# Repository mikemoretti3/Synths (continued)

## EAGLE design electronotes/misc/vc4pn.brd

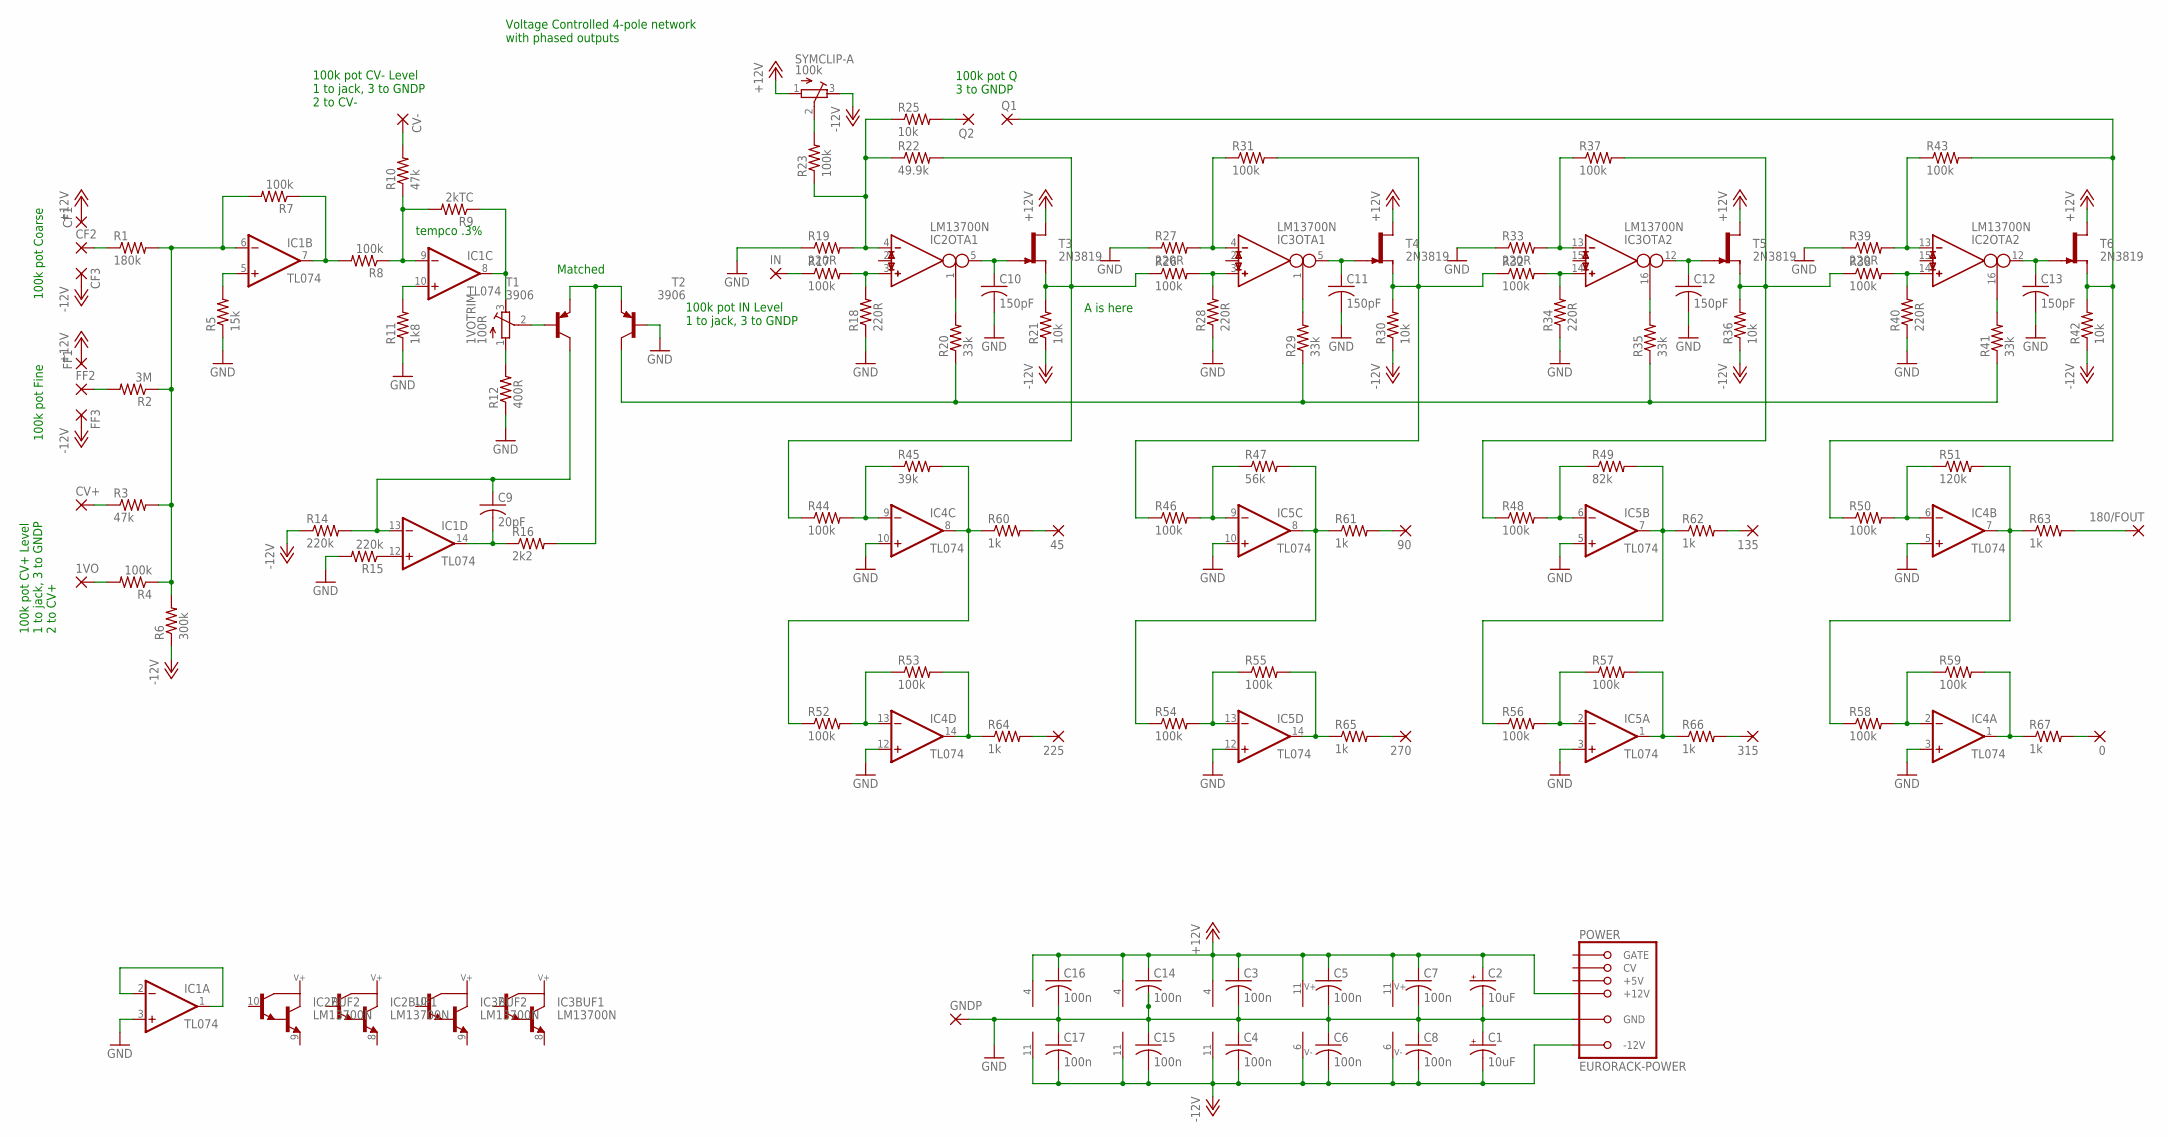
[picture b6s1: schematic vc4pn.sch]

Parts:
0, 1VO, 45, 90, 135, 180/FOUT, 225, 270, 315: 2,54/1,0
1VOTRIM: 100R; RTRIM64W
C1, C2: 10uF; E2,5-5
C3, C4, C5, C6, C7, C8, C14, C15, C16, C17: 100n; C050-025X075
C9: 20pF; C050-025X075
C10, C11, C12, C13: 150pF; C050-025X075
CF1, CF2, CF3: 2,54/1,0
CV+: 2,54/1,0
CV-: 2,54/1,0
FF1, FF2, FF3: 2,54/1,0
GNDP: 2,54/1,0
IC1, IC4, IC5: TL074; DIL14
IC2, IC3: LM13700N; DIL16
IN: 2,54/1,0
POWER: EURORACK-POWER; PINSHRD_PTH_2X8
Q1, Q2: 2,54/1,0
R1: 180k; 0207/2V
R2: 3M; 0207/2V
R3, R10: 47k; 0207/2V
R4, R7, R8, R17, R23, R26, R31, R32, R37, R38, R43, R44, R46, R48, R50, R52, R53, R54, R55, R56, R57, R58, R59: 100k; 0207/2V
R5: 15k; 0207/2V
R6: 300k; 0207/2V
R9: 2kTC; 0207/10
R11: 1k8; 0207/2V
R12: 400R; 0207/2V
R14, R15: 220k; 0207/2V
R16: 2k2; 0207/2V
R18, R19, R27, R28, R33, R34, R39, R40: 220R; 0207/2V
R20, R29, R35, R41: 33k; 0207/2V
R21, R25, R30, R36, R42: 10k; 0207/2V
R22: 49.9k; 0207/2V
R45: 39k; 0207/2V
R47: 56k; 0207/2V
R49: 82k; 0207/2V
R51: 120k; 0207/2V
R60, R61, R62, R63, R64, R65, R66, R67: 1k; 0207/2V
SYMCLIP-A: 100k; RTRIM64W
T1, T2: 3906; TO92-EBC
T3, T4, T5, T6: 2N3819; TO92-

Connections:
+12V: C2.+, C3.1, C5.1, C7.1, C14.1, C16.1, CF1.1, FF1.1, IC1.4 (V+), IC2.11 (7), IC3.11 (7), IC4.4 (V+), IC5.4 (V+), POWER.+12V@1 (+12V), POWER.+12V@2 (+12V), SYMCLIP-A.1 (A), T3.3 (D), T4.3 (D), T5.3 (D), T6.3 (D)
-12V: C1.-, C4.2, C6.2, C8.2, C15.2, C17.2, CF3.1, FF3.1, IC1.11 (V-), IC2.6 (4), IC3.6 (4), IC4.11 (V-), IC5.11 (V-), POWER.-12V@1 (-12V), POWER.-12V@2 (-12V), R6.1, R14.1, R21.1, R30.1, R36.1, R42.1, SYMCLIP-A.3 (E)
GND: C1.+, C2.-, C3.2, C4.1, C5.2, C6.1, C7.2, C8.1, C10.2, C11.2, C12.2, C13.2, C14.2, C15.1, C16.2, C17.1, GNDP.1, IC1.3 (+IN), IC4.3 (+IN), IC4.5 (+IN), IC4.10 (+IN), IC4.12 (+IN), IC5.3 (+IN), IC5.5 (+IN), IC5.10 (+IN), IC5.12 (+IN), POWER.GND@1 (GND), POWER.GND@2 (GND), POWER.GND@3 (GND), POWER.GND@4 (GND), POWER.GND@5 (GND), POWER.GND@6 (GND), R5.1, R11.1, R12.1, R15.2, R18.1, R19.1, R27.1, R28.1, R33.1, R34.1, R39.1, R40.1, T2.B
unnamed: CF2.1, R1.1
unnamed: FF2.1, R2.2
unnamed: CV+.1, R3.1
unnamed: IC1.1 (OUT), IC1.2 (-IN)
unnamed: 1VO.1, R4.2
unnamed: IC1.5 (+IN), R5.2
unnamed: CV-.1, R10.2
unnamed: IC1.6 (-IN), R1.2, R2.1, R3.2, R4.1, R6.2, R7.2
unnamed: IC1.7 (OUT), R7.1, R8.2
unnamed: IC1.9 (-IN), R8.1, R9.2, R10.1
unnamed: 1VOTRIM.3 (E), IC1.8 (OUT), R9.1
unnamed: 1VOTRIM.1 (A), R12.2
unnamed: IC1.10 (+IN), R11.2
unnamed: R16.2, T1.E, T2.E
unnamed: 1VOTRIM.2 (S), T1.B
unnamed: C9.1, IC1.13 (-IN), R14.2, T1.C
unnamed: IC1.12 (+IN), R15.1
unnamed: C9.2, IC1.14 (OUT), R16.1
unnamed: IN.1, R17.1
unnamed: IC2.3 (IN_P), R17.2, R18.2
unnamed: IC2.4 (IN_N), R19.2, R22.1, R23.1, R25.1
unnamed: IC2.1 (I_BIAS), R20.2
unnamed: R20.1, R29.1, R35.1, R41.1, T2.C
unnamed: C10.1, IC2.5 (OUT), T3.2 (G)
unnamed: R21.2, R22.2, R26.1, R44.1, T3.1 (S)
unnamed: IC3.3 (IN_P), R26.2, R28.2
unnamed: R23.2, SYMCLIP-A.2 (S)
unnamed: IC3.4 (IN_N), R27.2, R31.1
unnamed: IC3.1 (I_BIAS), R29.2
unnamed: Q2.1, R25.2
unnamed: C11.1, IC3.5 (OUT), T4.2 (G)
unnamed: R30.2, R31.2, R32.1, R46.1, T4.1 (S)
unnamed: IC4.9 (-IN), R44.2, R45.1
unnamed: IC5.9 (-IN), R46.2, R47.1
unnamed: IC3.14 (IN_P), R32.2, R34.2
unnamed: IC3.13 (IN_N), R33.2, R37.1
unnamed: IC3.16 (I_BIAS), R35.2
unnamed: C12.1, IC3.12 (OUT), T5.2 (G)
unnamed: R36.2, R37.2, R38.1, R48.1, T5.1 (S)
unnamed: IC5.6 (-IN), R48.2, R49.1
unnamed: IC4.6 (-IN), R50.2, R51.1
unnamed: IC2.14 (IN_P), R38.2, R40.2
unnamed: IC2.13 (IN_N), R39.2, R43.1
unnamed: IC2.16 (I_BIAS), R41.2
unnamed: C13.1, IC2.12 (OUT), T6.2 (G)
unnamed: Q1.1, R42.2, R43.2, R50.1, T6.1 (S)
unnamed: IC4.13 (-IN), R52.2, R53.1
unnamed: IC5.13 (-IN), R54.2, R55.1
unnamed: IC5.2 (-IN), R56.2, R57.1
unnamed: IC4.2 (-IN), R58.2, R59.1
unnamed: IC4.8 (OUT), R45.2, R52.1, R60.1
unnamed: IC5.8 (OUT), R47.2, R54.1, R61.1
unnamed: IC5.7 (OUT), R49.2, R56.1, R62.1
unnamed: IC4.7 (OUT), R51.2, R58.1, R63.1
unnamed: IC4.14 (OUT), R53.2, R64.1
unnamed: IC5.14 (OUT), R55.2, R65.1
unnamed: IC5.1 (OUT), R57.2, R66.1
unnamed: IC4.1 (OUT), R59.2, R67.1
unnamed: 45.1, R60.2
unnamed: 90.1, R61.2
unnamed: 135.1, R62.2
unnamed: 180/FOUT.1, R63.2
unnamed: 225.1, R64.2
unnamed: 270.1, R65.2
unnamed: 315.1, R66.2
unnamed: 0.1, R67.2

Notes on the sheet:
Matched
100k pot CV+ Level 1 to jack, 3 to GNDP 2 to CV+
100k pot Coarse
100k pot Fine
100k pot CV- Level 1 to jack, 3 to GNDP 2 to CV-
tempco .3%
100k pot IN Level 1 to jack, 3 to GNDP
100k pot Q 3 to GNDP
A is here
Voltage Controlled 4-pole network with phased outputs

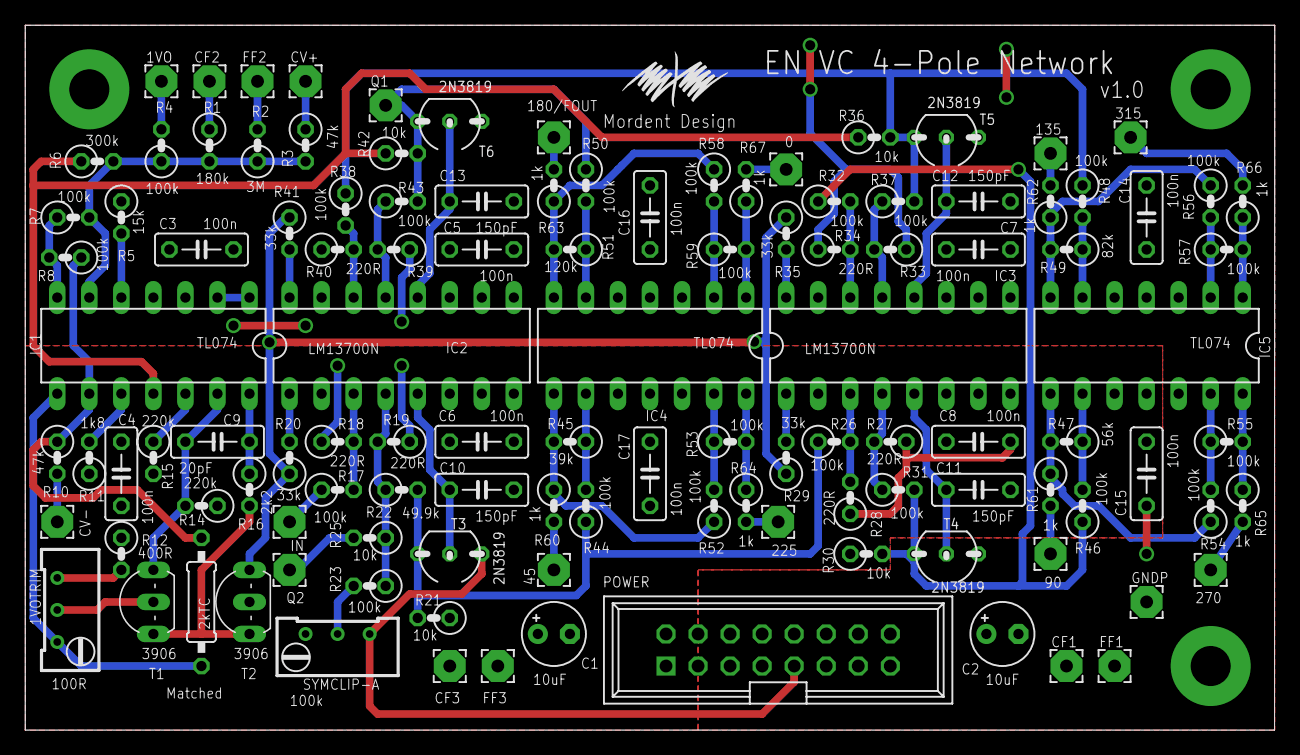
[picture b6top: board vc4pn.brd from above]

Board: 2 copper layers, 99.1 x 55.9 mm, 117 parts (0 on the bottom side), 69 nets.

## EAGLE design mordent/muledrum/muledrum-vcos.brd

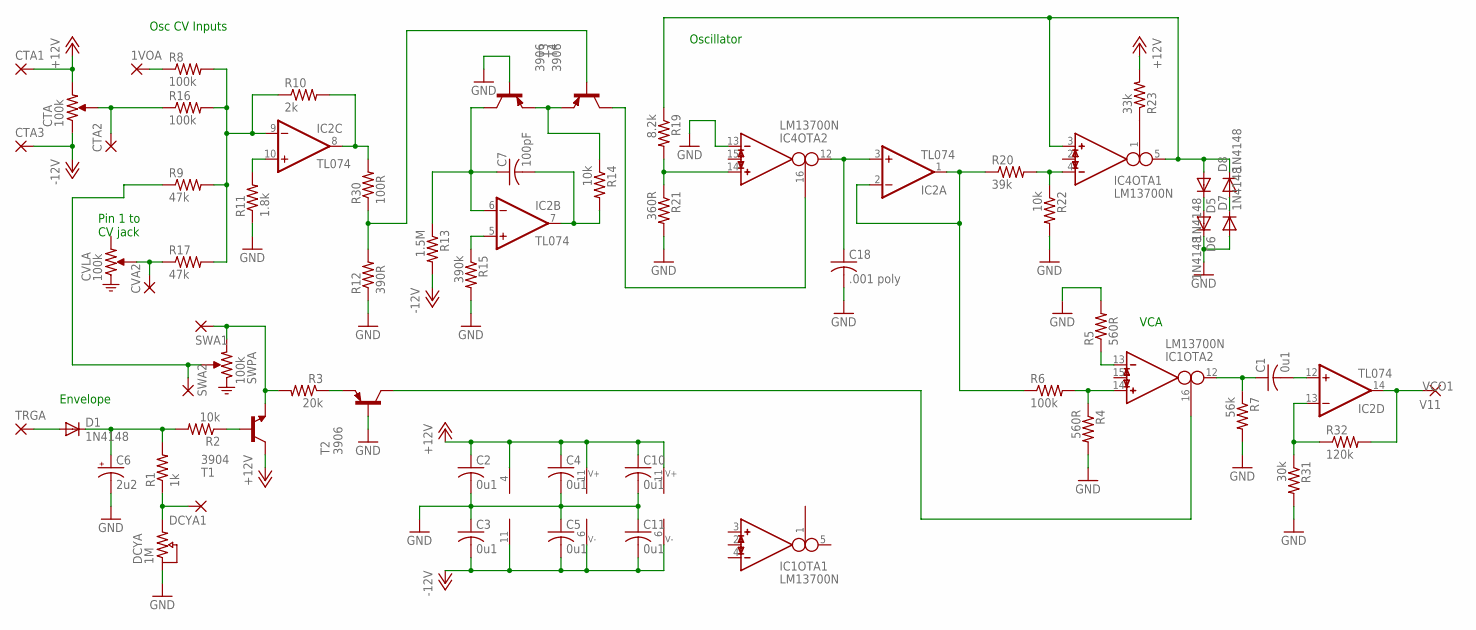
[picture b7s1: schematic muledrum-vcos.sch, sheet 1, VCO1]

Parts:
1VOA: 2,54/1,0
C1, C2, C3, C4, C5, C10, C11: 0u1; C050-025X075
C6: 2u2; E2,5-5
C7: 100pF; C050-025X075
C18: .001 poly; C050-025X075
CTA1, CTA2, CTA3: 2,54/1,0
CVA2: 2,54/1,0
D1, D5, D6, D7, D8: 1N4148; DO35-7
DCYA1: 2,54/1,0
IC1, IC4: LM13700N; DIL16
IC2: TL074; DIL14
R1: 1k; 0207/10
R2, R14, R22: 10k; 0207/10
R3: 20k; 0207/10
R4, R5: 560R; 0207/10
R6, R8, R16: 100k; 0207/10
R7: 56k; 0207/10
R9, R17: 47k; 0207/10
R10: 2k; 0207/10
R11: 1.8k; 0207/10
R12: 390R; 0207/10
R13: 1.5M; 0207/10
R15: 390k; 0207/10
R19: 8.2k; 0207/10
R20: 39k; 0207/10
R21: 360R; 0207/10
R23: 33k; 0207/10
R30: 100R; 0207/10
R31: 30k; 0207/10
R32: 120k; 0207/10
SWA1, SWA2: 2,54/1,0
T1: 3904; TO92-EBC
T2, T3, T4: 3906; TO92-EBC
TRGA: 2,54/1,0
V11: 2,54/1,0

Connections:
+12V: C2.1, C4.1, C10.1, CTA1.1, IC1.11 (7), IC2.4 (V+), IC4.11 (7), R23.2, T1.C; also elsewhere on the board
-12V: C3.2, C5.2, C11.2, CTA3.1, IC1.6 (4), IC2.11 (V-), IC4.6 (4), R13.2; also elsewhere on the board
GND: C2.2, C3.1, C4.2, C5.1, C6.-, C10.2, C11.1, C18.2, D6.C, D7.A, IC4.13 (IN_N), R4.2, R5.2, R7.2, R11.1, R12.1, R15.2, R21.2, R22.2, R31.2, T2.B, T4.B; also elsewhere on the board
unnamed: R2.1, T1.B
unnamed: R3.2, SWA1.1, T1.E
unnamed: R3.1, T2.E
unnamed: C6.+, D1.C, R1.2, R2.2
unnamed: DCYA1.1, R1.1
unnamed: IC1.16 (I_BIAS), T2.C
unnamed: IC1.14 (IN_P), R4.1, R6.2
unnamed: IC1.13 (IN_N), R5.1
unnamed: C1.1, IC1.12 (OUT), R7.1
unnamed: D1.A, TRGA.1
unnamed: R9.1, SWA2.1
unnamed: CTA2.1, R16.1
unnamed: C1.2, IC2.12 (+IN)
unnamed: 1VOA.1, R8.1
unnamed: IC2.10 (+IN), R11.2
unnamed: IC2.9 (-IN), R8.2, R9.2, R10.1, R16.2, R17.2
unnamed: IC2.8 (OUT), R10.2, R30.2
unnamed: IC2.13 (-IN), R31.1, R32.1
unnamed: R14.1, T3.E, T4.E
unnamed: CVA2.1, R17.1
unnamed: C7.1, IC2.6 (-IN), R13.1, T4.C
unnamed: C7.2, IC2.7 (OUT), R14.2
unnamed: IC2.5 (+IN), R15.1
unnamed: R12.2, R30.1, T3.B
unnamed: IC4.16 (I_BIAS), T3.C
unnamed: IC4.14 (IN_P), R19.2, R21.1
unnamed: IC4.4 (IN_N), R20.2, R22.1
unnamed: C18.1, IC2.3 (+IN), IC4.12 (OUT)
unnamed: IC4.1 (I_BIAS), R23.1
unnamed: D5.C, D6.A
unnamed: D7.C, D8.A
OSCOS: D5.A, D8.C, IC4.3 (IN_P), IC4.5 (OUT), R19.1
OSCOT: IC2.1 (OUT), IC2.2 (-IN), R6.1, R20.1
VCO1: IC2.14 (OUT), R32.2, V11.1

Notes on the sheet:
Osc CV Inputs
Oscillator
Pin 1 to CV jack
Envelope
VCA

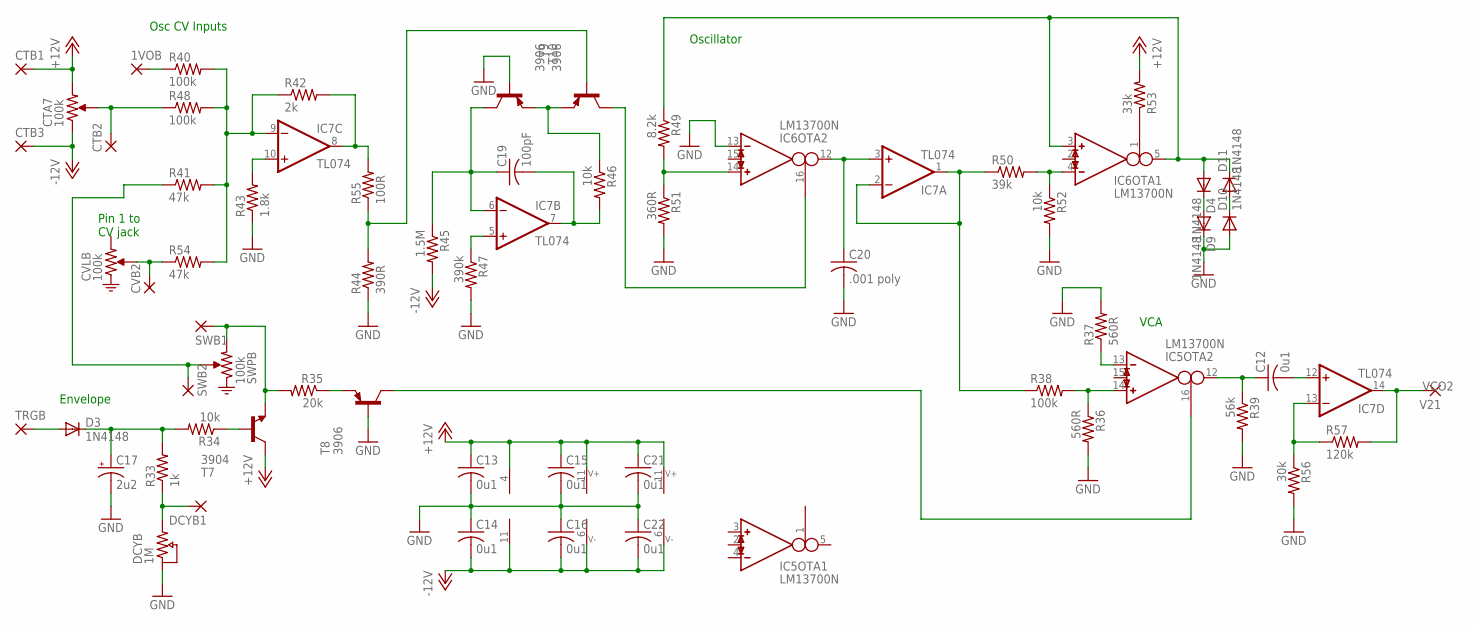
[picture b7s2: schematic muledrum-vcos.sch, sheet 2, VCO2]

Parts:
1VOB: 2,54/1,0
C12, C13, C14, C15, C16, C21, C22: 0u1; C050-025X075
C17: 2u2; E2,5-5
C19: 100pF; C050-025X075
C20: .001 poly; C050-025X075
CTB1, CTB2, CTB3: 2,54/1,0
CVB2: 2,54/1,0
D3, D4, D9, D10, D11: 1N4148; DO35-7
DCYB1: 2,54/1,0
IC5, IC6: LM13700N; DIL16
IC7: TL074; DIL14
R33: 1k; 0207/10
R34, R46, R52: 10k; 0207/10
R35: 20k; 0207/10
R36, R37: 560R; 0207/10
R38, R40, R48: 100k; 0207/10
R39: 56k; 0207/10
R41, R54: 47k; 0207/10
R42: 2k; 0207/10
R43: 1.8k; 0207/10
R44: 390R; 0207/10
R45: 1.5M; 0207/10
R47: 390k; 0207/10
R49: 8.2k; 0207/10
R50: 39k; 0207/10
R51: 360R; 0207/10
R53: 33k; 0207/10
R55: 100R; 0207/10
R56: 30k; 0207/10
R57: 120k; 0207/10
SWB1, SWB2: 2,54/1,0
T7: 3904; TO92-EBC
T8, T9, T10: 3906; TO92-EBC
TRGB: 2,54/1,0
V21: 2,54/1,0

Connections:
+12V: C13.1, C15.1, C21.1, CTB1.1, IC5.11 (7), IC6.11 (7), IC7.4 (V+), R53.2, T7.C; also elsewhere on the board
-12V: C14.2, C16.2, C22.2, CTB3.1, IC5.6 (4), IC6.6 (4), IC7.11 (V-), R45.2; also elsewhere on the board
GND: C13.2, C14.1, C15.2, C16.1, C17.-, C20.2, C21.2, C22.1, D9.C, D10.A, IC6.13 (IN_N), R36.2, R37.2, R39.2, R43.1, R44.1, R47.2, R51.2, R52.2, R56.2, T8.B, T10.B; also elsewhere on the board
unnamed: C17.+, D3.C, R33.2, R34.2
unnamed: R34.1, T7.B
unnamed: R35.2, SWB1.1, T7.E
unnamed: R35.1, T8.E
unnamed: IC5.14 (IN_P), R36.1, R38.2
unnamed: IC5.13 (IN_N), R37.1
unnamed: C12.1, IC5.12 (OUT), R39.1
unnamed: D3.A, TRGB.1
unnamed: DCYB1.1, R33.1
unnamed: R41.1, SWB2.1
unnamed: 1VOB.1, R40.1
unnamed: IC7.10 (+IN), R43.2
unnamed: IC7.9 (-IN), R40.2, R41.2, R42.1, R48.2, R54.2
unnamed: IC7.8 (OUT), R42.2, R55.2
unnamed: R46.1, T9.E, T10.E
unnamed: C19.1, IC7.6 (-IN), R45.1, T10.C
unnamed: C19.2, IC7.7 (OUT), R46.2
unnamed: IC7.5 (+IN), R47.1
unnamed: R44.2, R55.1, T9.B
unnamed: IC6.14 (IN_P), R49.2, R51.1
unnamed: IC6.4 (IN_N), R50.2, R52.1
unnamed: IC6.1 (I_BIAS), R53.1
unnamed: D4.C, D9.A
unnamed: D10.C, D11.A
unnamed: C20.1, IC6.12 (OUT), IC7.3 (+IN)
unnamed: CVB2.1, R54.1
unnamed: IC6.16 (I_BIAS), T9.C
unnamed: IC5.16 (I_BIAS), T8.C
unnamed: C12.2, IC7.12 (+IN)
unnamed: IC7.13 (-IN), R56.1, R57.1
unnamed: CTB2.1, R48.1
OSCOS1: D4.A, D11.C, IC6.3 (IN_P), IC6.5 (OUT), R49.1
OSCOT1: IC7.1 (OUT), IC7.2 (-IN), R38.1, R50.1
VCO2: IC7.14 (OUT), R57.2, V21.1

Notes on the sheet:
Osc CV Inputs
Oscillator
Pin 1 to CV jack
Envelope
VCA

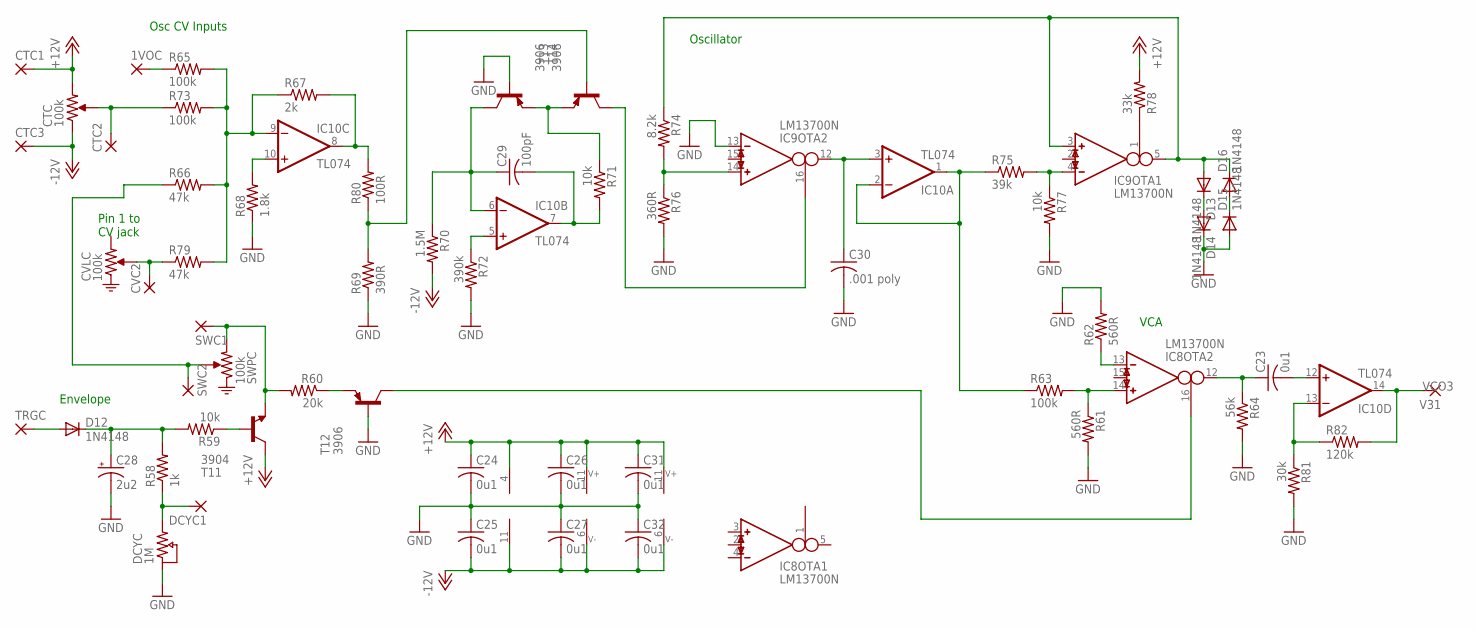
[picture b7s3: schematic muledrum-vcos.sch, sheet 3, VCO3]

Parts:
1VOC: 2,54/1,0
C23, C24, C25, C26, C27, C31, C32: 0u1; C050-025X075
C28: 2u2; E2,5-5
C29: 100pF; C050-025X075
C30: .001 poly; C050-025X075
CTC1, CTC2, CTC3: 2,54/1,0
CVC2: 2,54/1,0
D12, D13, D14, D15, D16: 1N4148; DO35-7
DCYC1: 2,54/1,0
IC8, IC9: LM13700N; DIL16
IC10: TL074; DIL14
R58: 1k; 0207/10
R59, R71, R77: 10k; 0207/10
R60: 20k; 0207/10
R61, R62: 560R; 0207/10
R63, R65, R73: 100k; 0207/10
R64: 56k; 0207/10
R66, R79: 47k; 0207/10
R67: 2k; 0207/10
R68: 1.8k; 0207/10
R69: 390R; 0207/10
R70: 1.5M; 0207/10
R72: 390k; 0207/10
R74: 8.2k; 0207/10
R75: 39k; 0207/10
R76: 360R; 0207/10
R78: 33k; 0207/10
R80: 100R; 0207/10
R81: 30k; 0207/10
R82: 120k; 0207/10
SWC1, SWC2: 2,54/1,0
T11: 3904; TO92-EBC
T12, T13, T14: 3906; TO92-EBC
TRGC: 2,54/1,0
V31: 2,54/1,0

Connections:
+12V: C24.1, C26.1, C31.1, CTC1.1, IC8.11 (7), IC9.11 (7), IC10.4 (V+), R78.2, T11.C; also elsewhere on the board
-12V: C25.2, C27.2, C32.2, CTC3.1, IC8.6 (4), IC9.6 (4), IC10.11 (V-), R70.2; also elsewhere on the board
GND: C24.2, C25.1, C26.2, C27.1, C28.-, C30.2, C31.2, C32.1, D14.C, D15.A, IC9.13 (IN_N), R61.2, R62.2, R64.2, R68.1, R69.1, R72.2, R76.2, R77.2, R81.2, T12.B, T14.B; also elsewhere on the board
unnamed: C28.+, D12.C, R58.2, R59.2
unnamed: R59.1, T11.B
unnamed: R60.2, SWC1.1, T11.E
unnamed: R60.1, T12.E
unnamed: IC8.14 (IN_P), R61.1, R63.2
unnamed: IC8.13 (IN_N), R62.1
unnamed: C23.1, IC8.12 (OUT), R64.1
unnamed: D12.A, TRGC.1
unnamed: DCYC1.1, R58.1
unnamed: R66.1, SWC2.1
unnamed: 1VOC.1, R65.1
unnamed: IC10.10 (+IN), R68.2
unnamed: IC10.9 (-IN), R65.2, R66.2, R67.1, R73.2, R79.2
unnamed: IC10.8 (OUT), R67.2, R80.2
unnamed: R71.1, T13.E, T14.E
unnamed: C29.1, IC10.6 (-IN), R70.1, T14.C
unnamed: C29.2, IC10.7 (OUT), R71.2
unnamed: IC10.5 (+IN), R72.1
unnamed: R69.2, R80.1, T13.B
unnamed: IC9.14 (IN_P), R74.2, R76.1
unnamed: IC9.4 (IN_N), R75.2, R77.1
unnamed: IC9.1 (I_BIAS), R78.1
unnamed: D13.C, D14.A
unnamed: D15.C, D16.A
unnamed: C30.1, IC9.12 (OUT), IC10.3 (+IN)
unnamed: CVC2.1, R79.1
unnamed: IC9.16 (I_BIAS), T13.C
unnamed: IC8.16 (I_BIAS), T12.C
unnamed: C23.2, IC10.12 (+IN)
unnamed: IC10.13 (-IN), R81.1, R82.1
unnamed: CTC2.1, R73.1
OSCOS2: D13.A, D16.C, IC9.3 (IN_P), IC9.5 (OUT), R74.1
OSCOT2: IC10.1 (OUT), IC10.2 (-IN), R63.1, R75.1
VCO3: IC10.14 (OUT), R82.2, V31.1

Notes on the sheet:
Osc CV Inputs
Oscillator
Pin 1 to CV jack
Envelope
VCA

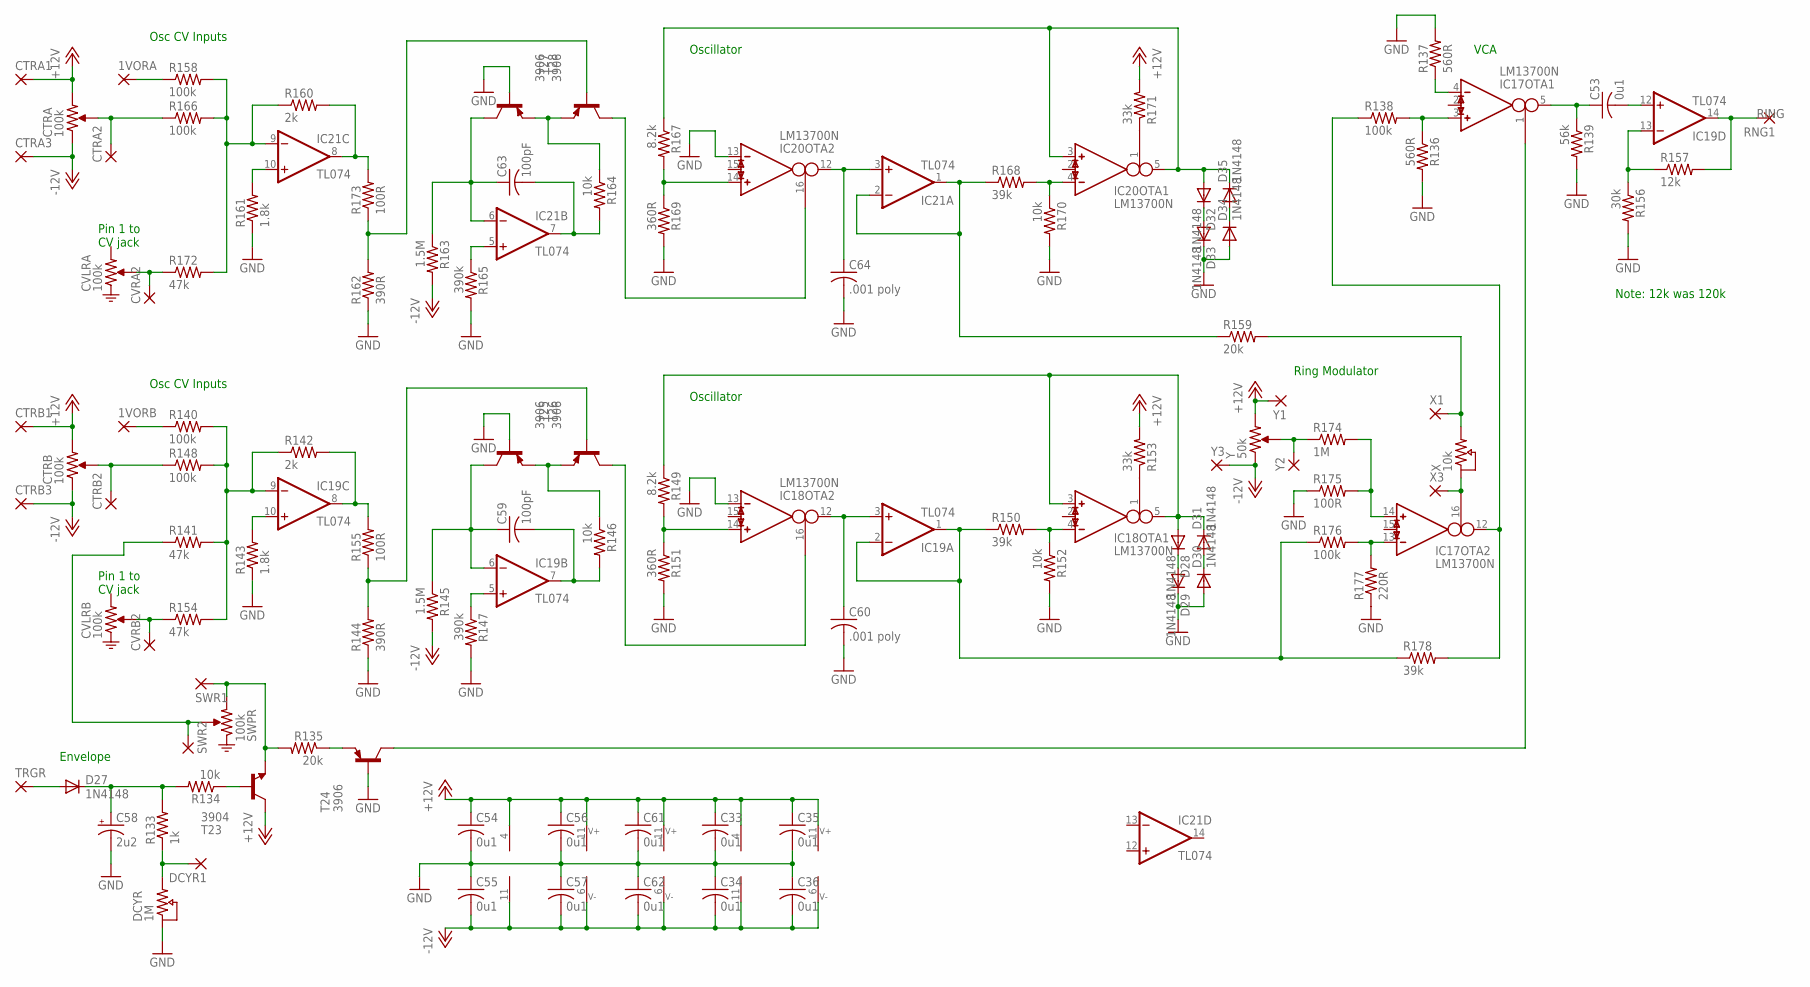
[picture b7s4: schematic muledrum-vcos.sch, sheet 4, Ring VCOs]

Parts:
1VORA, 1VORB: 2,54/1,0
C33, C34, C35, C36, C53, C54, C55, C56, C57, C61, C62: 0u1; C050-025X075
C58: 2u2; E2,5-5
C59, C63: 100pF; C050-025X075
C60, C64: .001 poly; C050-025X075
CTRA1, CTRA2, CTRA3: 2,54/1,0
CTRB1, CTRB2, CTRB3: 2,54/1,0
CVRA2: 2,54/1,0
CVRB2: 2,54/1,0
D27, D28, D29, D30, D31, D32, D33, D34, D35: 1N4148; DO35-7
DCYR1: 2,54/1,0
IC17, IC18, IC20: LM13700N; DIL16
IC19, IC21: TL074; DIL14
R133: 1k; 0207/10
R134, R146, R152, R164, R170: 10k; 0207/10
R135, R159: 20k; 0207/10
R136, R137: 560R; 0207/10
R138, R140, R148, R158, R166, R176: 100k; 0207/10
R139: 56k; 0207/10
R141, R154, R172: 47k; 0207/10
R142, R160: 2k; 0207/10
R143, R161: 1.8k; 0207/10
R144, R162: 390R; 0207/10
R145, R163: 1.5M; 0207/10
R147, R165: 390k; 0207/10
R149, R167: 8.2k; 0207/10
R150, R168, R178: 39k; 0207/10
R151, R169: 360R; 0207/10
R153, R171: 33k; 0207/10
R155, R173, R175: 100R; 0207/10
R156: 30k; 0207/10
R157: 12k; 0207/10
R174: 1M; 0207/10
R177: 220R; 0207/10
RNG1: 2,54/1,0
SWR1, SWR2: 2,54/1,0
T23: 3904; TO92-EBC
T24, T25, T26, T27, T28: 3906; TO92-EBC
TRGR: 2,54/1,0
X1, X3: 2,54/1,0
Y1, Y2, Y3: 2,54/1,0

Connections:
+12V: C33.1, C35.1, C54.1, C56.1, C61.1, CTRA1.1, CTRB1.1, IC17.11 (7), IC18.11 (7), IC19.4 (V+), IC20.11 (7), IC21.4 (V+), R153.2, R171.2, T23.C, Y1.1; also elsewhere on the board
-12V: C34.2, C36.2, C55.2, C57.2, C62.2, CTRA3.1, CTRB3.1, IC17.6 (4), IC18.6 (4), IC19.11 (V-), IC20.6 (4), IC21.11 (V-), R145.2, R163.2, Y3.1; also elsewhere on the board
GND: C33.2, C34.1, C35.2, C36.1, C54.2, C55.1, C56.2, C57.1, C58.-, C60.2, C61.2, C62.1, C64.2, D29.C, D30.A, D33.C, D34.A, IC18.13 (IN_N), IC20.13 (IN_N), R136.2, R137.2, R139.2, R143.1, R144.1, R147.2, R151.2, R152.2, R156.2, R161.1, R162.1, R165.2, R169.2, R170.2, R175.1, R177.1, T24.B, T26.B, T28.B; also elsewhere on the board
unnamed: C58.+, D27.C, R133.2, R134.2
unnamed: R134.1, T23.B
unnamed: R135.2, SWR1.1, T23.E
unnamed: R135.1, T24.E
unnamed: IC17.3 (IN_P), R136.1, R138.2
unnamed: IC17.4 (IN_N), R137.1
unnamed: C53.1, IC17.5 (OUT), R139.1
unnamed: D27.A, TRGR.1
unnamed: DCYR1.1, R133.1
unnamed: R141.1, SWR2.1
unnamed: 1VORB.1, R140.1
unnamed: IC19.10 (+IN), R143.2
unnamed: IC19.9 (-IN), R140.2, R141.2, R142.1, R148.2, R154.2
unnamed: IC19.8 (OUT), R142.2, R155.2
unnamed: R146.1, T25.E, T26.E
unnamed: C59.1, IC19.6 (-IN), R145.1, T26.C
unnamed: C59.2, IC19.7 (OUT), R146.2
unnamed: IC19.5 (+IN), R147.1
unnamed: R144.2, R155.1, T25.B
unnamed: IC18.14 (IN_P), R149.2, R151.1
unnamed: IC18.4 (IN_N), R150.2, R152.1
unnamed: IC18.1 (I_BIAS), R153.1
unnamed: D28.C, D29.A
unnamed: D30.C, D31.A
unnamed: C60.1, IC18.12 (OUT), IC19.3 (+IN)
unnamed: CVRB2.1, R154.1
unnamed: IC18.16 (I_BIAS), T25.C
unnamed: IC17.1 (I_BIAS), T24.C
unnamed: C53.2, IC19.12 (+IN)
unnamed: IC19.13 (-IN), R156.1, R157.1
unnamed: CTRB2.1, R148.1
unnamed: IC17.16 (I_BIAS), X3.1
unnamed: 1VORA.1, R158.1
unnamed: IC21.10 (+IN), R161.2
unnamed: IC21.9 (-IN), R158.2, R160.1, R166.2, R172.2
unnamed: IC21.8 (OUT), R160.2, R173.2
unnamed: R164.1, T27.E, T28.E
unnamed: C63.1, IC21.6 (-IN), R163.1, T28.C
unnamed: C63.2, IC21.7 (OUT), R164.2
unnamed: IC21.5 (+IN), R165.1
unnamed: R162.2, R173.1, T27.B
unnamed: IC20.14 (IN_P), R167.2, R169.1
unnamed: IC20.4 (IN_N), R168.2, R170.1
unnamed: IC20.1 (I_BIAS), R171.1
unnamed: D32.C, D33.A
unnamed: D34.C, D35.A
unnamed: C64.1, IC20.12 (OUT), IC21.3 (+IN)
unnamed: CVRA2.1, R172.1
unnamed: IC20.16 (I_BIAS), T27.C
unnamed: CTRA2.1, R166.1
unnamed: R159.2, X1.1
unnamed: R174.1, Y2.1
unnamed: IC17.14 (IN_P), R174.2, R175.2
unnamed: IC17.13 (IN_N), R176.2, R177.2
unnamed: IC17.12 (OUT), R138.1, R178.2
OSCOS5: D28.A, D31.C, IC18.3 (IN_P), IC18.5 (OUT), R149.1
OSCOS6: D32.A, D35.C, IC20.3 (IN_P), IC20.5 (OUT), R167.1
OSCOT5: IC19.1 (OUT), IC19.2 (-IN), R150.1, R176.1, R178.1
OSCOT6: IC21.1 (OUT), IC21.2 (-IN), R159.1, R168.1
RING: IC19.14 (OUT), R157.2, RNG1.1

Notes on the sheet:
Osc CV Inputs
Oscillator
Pin 1 to CV jack
Envelope
VCA
Ring Modulator
Note: 12k was 120k

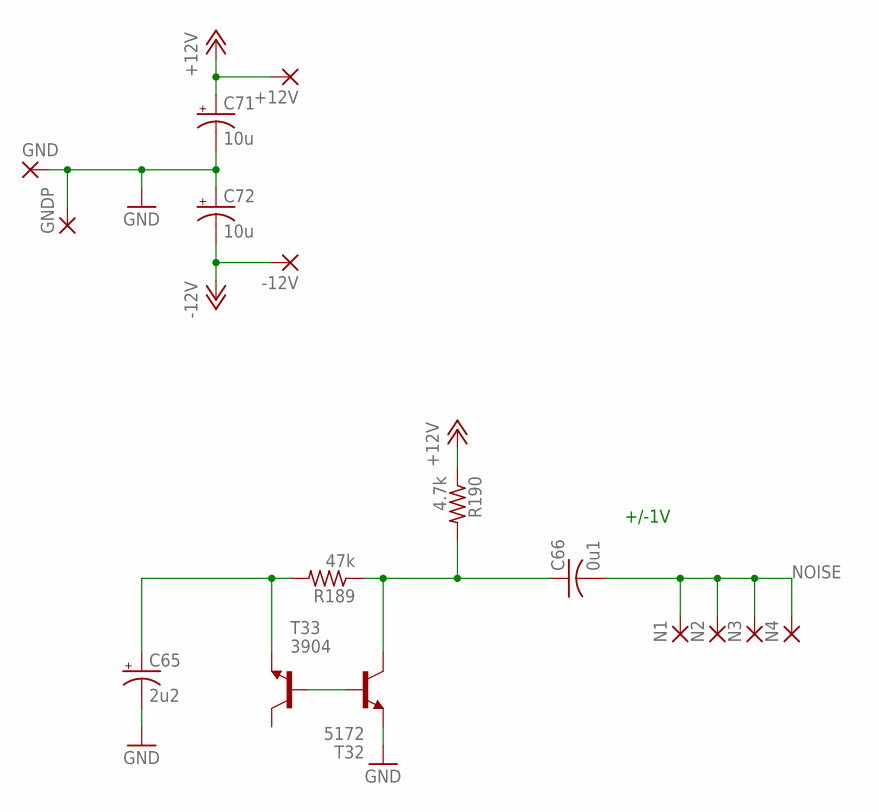
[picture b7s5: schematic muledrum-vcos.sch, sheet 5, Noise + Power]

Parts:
+12V: 2,54/1,0
-12V: 2,54/1,0
C65: 2u2; E2,5-5
C66: 0u1; C050-025X075
C71, C72: 10u; E2,5-5
GND: 2,54/1,0
GNDP: 2,54/1,0
N1, N2, N3, N4: 2,54/1,0
R189: 47k; 0207/10
R190: 4.7k; 0207/10
T32: 5172; TO92-ECB
T33: 3904; TO92-EBC

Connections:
+12V: +12V.1, C71.+, R190.1; also elsewhere on the board
-12V: -12V.1, C72.-; also elsewhere on the board
GND: C65.-, C71.-, C72.+, GND.1, GNDP.1, T33.E; also elsewhere on the board
unnamed: T32.B, T33.B
unnamed: C65.+, R189.2, T32.E
unnamed: C66.1, R189.1, R190.2, T33.C
NOISE: C66.2, N1.1, N2.1, N3.1, N4.1

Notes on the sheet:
+/-1V

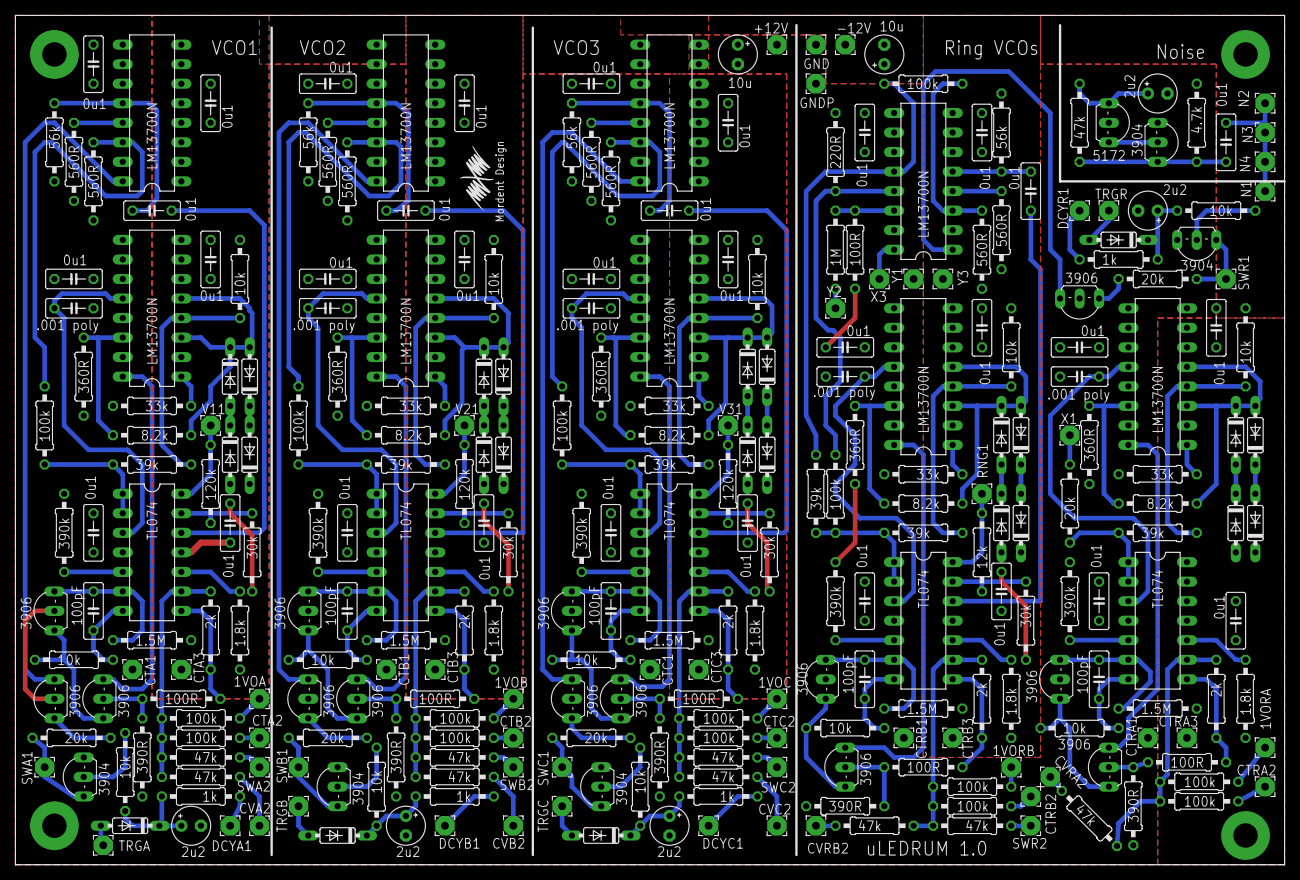
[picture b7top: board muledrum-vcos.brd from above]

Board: 2 copper layers, 165.1 x 110.5 mm, 289 parts (0 on the bottom side), 169 nets.

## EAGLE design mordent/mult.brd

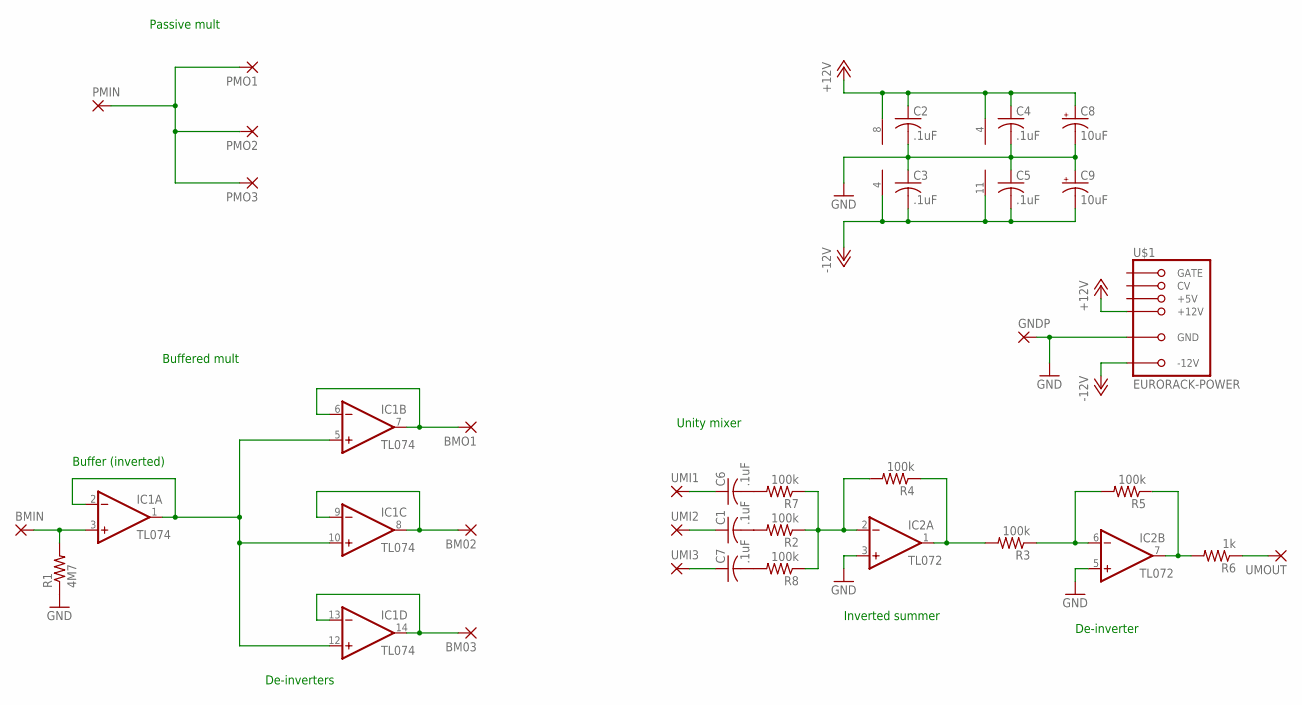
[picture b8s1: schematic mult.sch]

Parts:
BM02, BM03: 2,54/1,0
BMIN: 2,54/1,0
BMO1: 2,54/1,0
C1, C2, C3, C4, C5, C6, C7: .1uF; C050-025X075
C8, C9: 10uF; E2,5-5
GNDP: 2,54/1,0
IC1: TL074; DIL14
IC2: TL072; DIL08
PMIN: 2,54/1,0
PMO1, PMO2, PMO3: 2,54/1,0
R1: 4M7; 0207/10
R2, R3, R4, R5, R7, R8: 100k; 0207/10
R6: 1k; 0207/10
U$1: EURORACK-POWER; PINSHRD_PTH_2X8
UMI1, UMI2, UMI3: 2,54/1,0
UMOUT: 2,54/1,0

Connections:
+12V: C2.1, C4.1, C8.+, IC1.4 (V+), IC2.8 (V+), U$1.+12V@1 (+12V), U$1.+12V@2 (+12V)
-12V: C3.2, C5.2, C9.-, IC1.11 (V-), IC2.4 (V-), U$1.-12V@1 (-12V), U$1.-12V@2 (-12V)
GND: C2.2, C3.1, C4.2, C5.1, C8.-, C9.+, GNDP.1, IC2.3 (+IN), IC2.5 (+IN), R1.1, U$1.GND@1 (GND), U$1.GND@2 (GND), U$1.GND@3 (GND), U$1.GND@4 (GND), U$1.GND@5 (GND), U$1.GND@6 (GND)
unnamed: IC2.7 (OUT), R5.1, R6.2
unnamed: IC2.2 (-IN), R2.1, R4.2, R7.1, R8.1
unnamed: IC2.1 (OUT), R3.2, R4.1
unnamed: IC2.6 (-IN), R3.1, R5.2
unnamed: C1.2, R2.2
unnamed: R6.1, UMOUT.1
unnamed: C6.1, UMI1.1
unnamed: C6.2, R7.2
unnamed: C1.1, UMI2.1
unnamed: C7.2, R8.2
unnamed: C7.1, UMI3.1
unnamed: BMIN.1, IC1.3 (+IN), R1.2
unnamed: IC1.1 (OUT), IC1.2 (-IN), IC1.5 (+IN), IC1.10 (+IN), IC1.12 (+IN)
unnamed: BM03.1, IC1.13 (-IN), IC1.14 (OUT)
unnamed: BM02.1, IC1.8 (OUT), IC1.9 (-IN)
unnamed: BMO1.1, IC1.6 (-IN), IC1.7 (OUT)
PMULT: PMIN.1, PMO1.1, PMO2.1, PMO3.1

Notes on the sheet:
Passive mult
Buffered mult
Unity mixer
Inverted summer
De-inverter
Buffer (inverted)
De-inverters

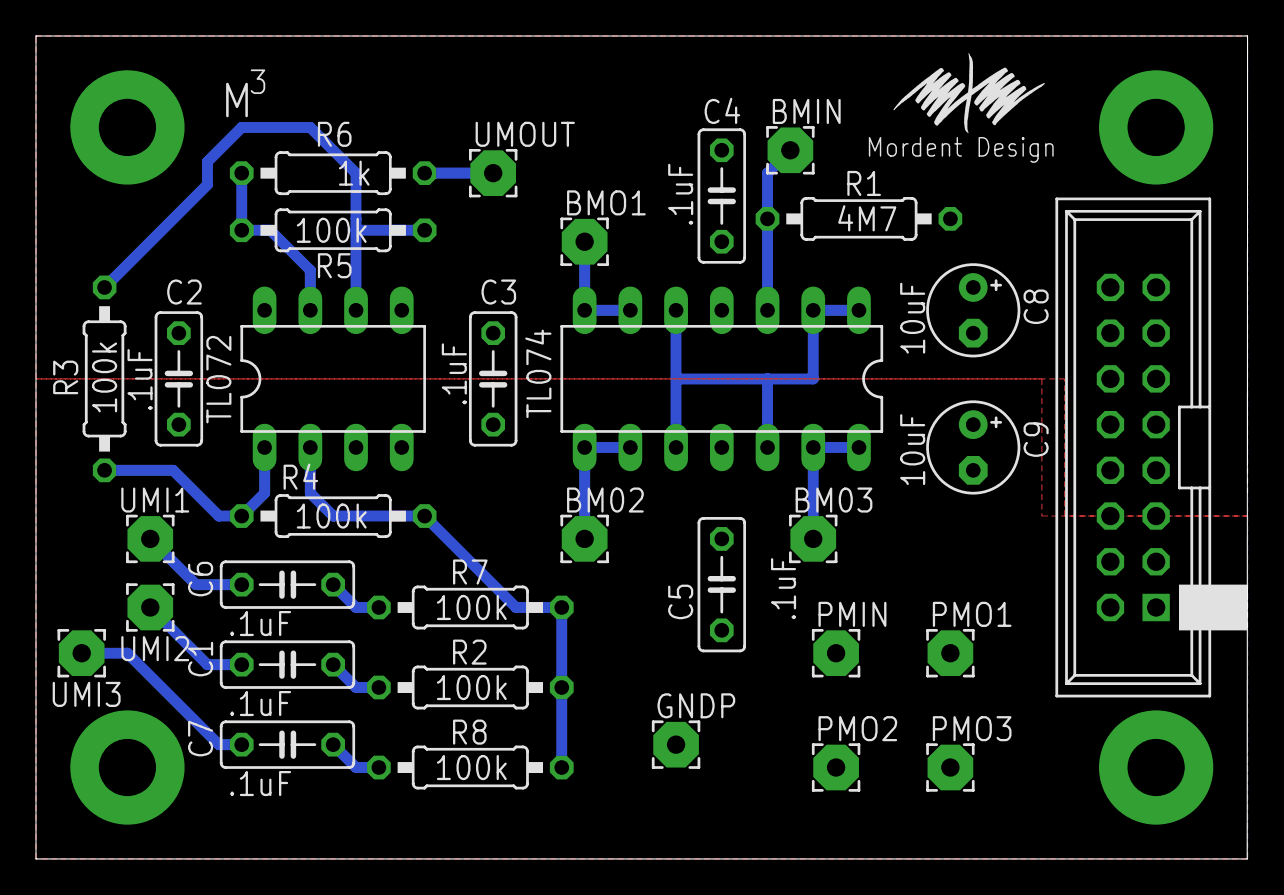
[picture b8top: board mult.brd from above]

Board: 2 copper layers, 67.3 x 45.7 mm, 33 parts (0 on the bottom side), 20 nets.

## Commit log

2017-06-22 Initial working modules. Some need updated docs on the schematics. Will update that later.
2018-03-12 Add more working boards
2018-03-12 Add docs and fixed vco1
2018-03-12 Add missing 12v conversion jpg
2018-03-12 Add readme
2018-03-12 Fix formatting
2018-03-12 Damn formatting again
2018-06-20 Add SEM1a vcf bom
2018-06-20 Add pots/jacks
2018-07-01 Add SEM1A panel
2018-08-19 Add new versions of the high ripple vcf and vocal filter
2018-08-19 Add missing boms and new boards/schematics
2018-09-05 Add triple bandpass board designed based on numerous EN filter bank articles.
2018-09-05 Move triple bandpass and add pdfs for it
2018-11-03 Remove mfos stuff
2018-12-20 Update parts
2019-06-06 Add back previous version of HR VCF
2019-06-06 Add pdf
2019-06-17 Add sem sch pdf
2019-10-15 Add pot symbols to make things clearer
2019-10-15 Add pot symbols to make things clearer.
